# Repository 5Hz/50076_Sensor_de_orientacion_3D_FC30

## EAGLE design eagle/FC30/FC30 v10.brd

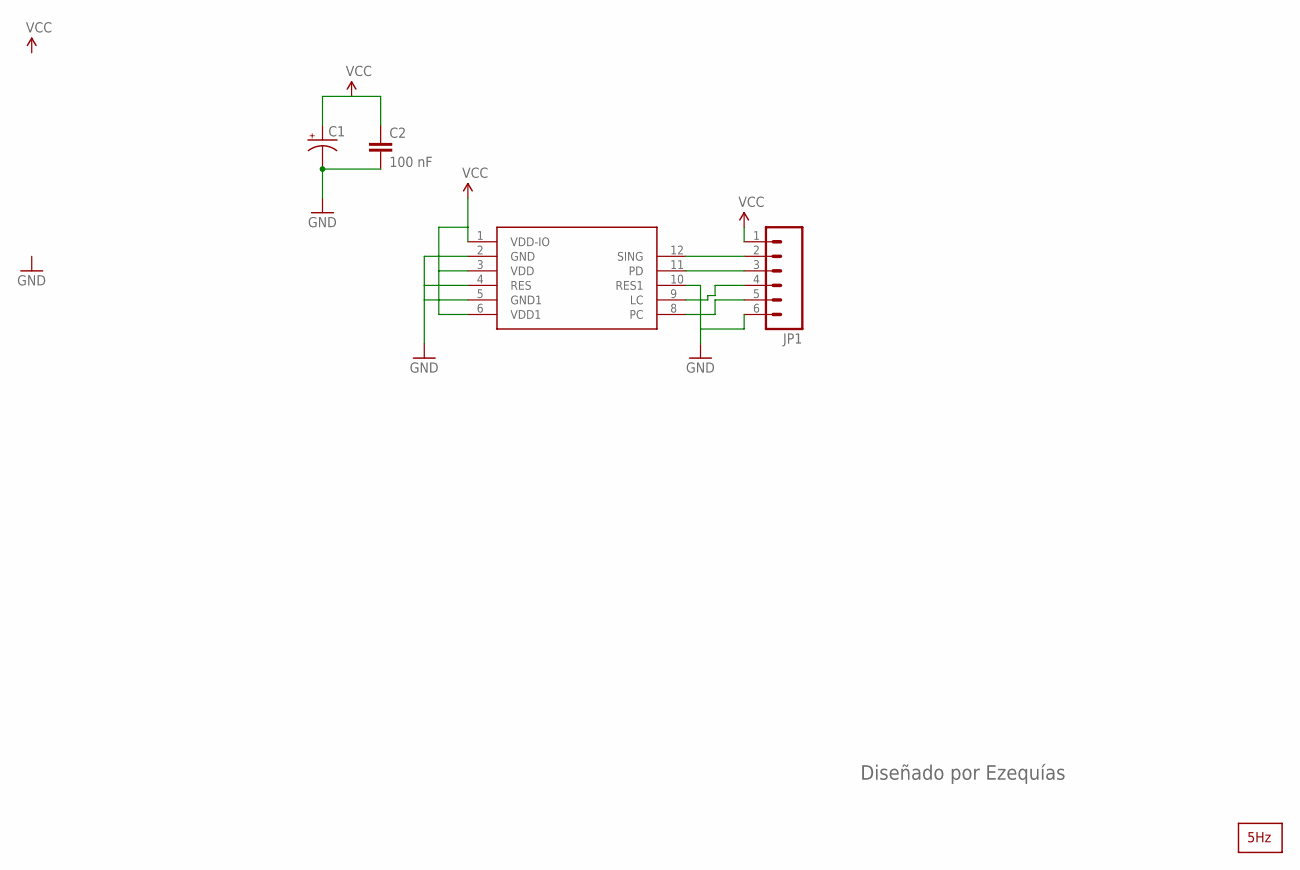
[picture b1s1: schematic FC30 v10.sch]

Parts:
C1: CAP_POL1206; EIA3216
C2: 100 nF; 0603-CAP
JP1: M06SIP; 1X06
U$1: FC30; LGA-14
U$2: LOGO2_SILK5MM; LOGO2_5MM

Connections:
GND: C1.C (-), C2.2, JP1.6, U$1.2 (GND), U$1.4 (RES), U$1.5 (GND1), U$1.10 (RES1)
unnamed: JP1.5, U$1.8 (PC)
unnamed: JP1.4, U$1.9 (LC)
unnamed: JP1.3, U$1.11 (PD)
unnamed: JP1.2, U$1.12 (SING)
VCC: C1.A (+), C2.1, JP1.1, U$1.1 (VDD-IO), U$1.3 (VDD), U$1.6 (VDD1)

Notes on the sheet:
Diseñado por Ezequías

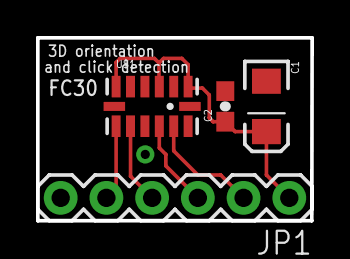
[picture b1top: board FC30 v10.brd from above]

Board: 2 copper layers, 15.2 x 10.2 mm, 5 parts (1 on the bottom side), 6 nets.

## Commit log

2014-01-13 creación

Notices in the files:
parts and their libraries:
SparkFun: Licensing: CC v3.0 Share-Alike You are welcome to use this library for commercial purposes.
